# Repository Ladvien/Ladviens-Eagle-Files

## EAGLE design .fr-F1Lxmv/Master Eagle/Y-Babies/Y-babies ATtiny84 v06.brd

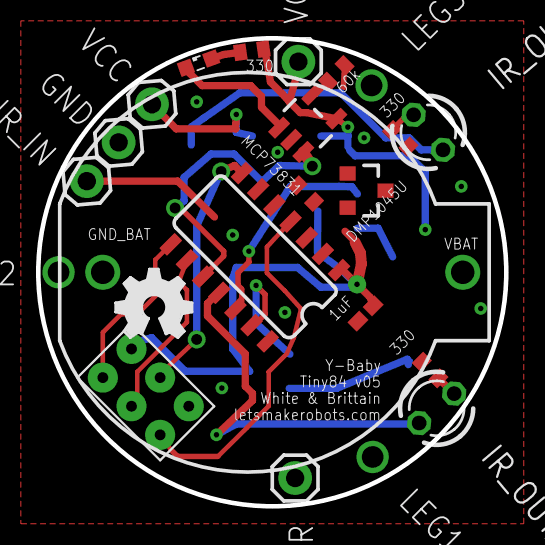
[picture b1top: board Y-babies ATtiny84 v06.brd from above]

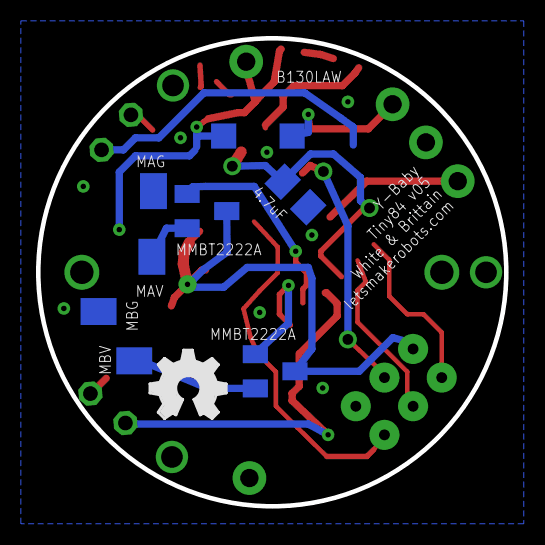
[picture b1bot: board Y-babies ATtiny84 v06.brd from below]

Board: 2 copper layers, 26.0 x 26.0 mm, 29 parts (9 on the bottom side), 20 nets.

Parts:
BAT1: LIR2032; BATTCOM_20MM_PTH
C1: 1uF; C0402K
C2: 4.7uF; C0805K
D1: B130LAW; SOD123
DMP1045U: MOSFET-PCHANNELSMD; SOT23-3
GND: M01PTH; 1X01
GND_BAR: M01PTH; 1X01
IR_IN: M01PTH; 1X01
IR_OUT_A: LED3MM
IR_OUT_B: LED3MM
LED1: SML0603
MMBT2222A_L, MMBT2222A_R: SOT23
MOT_1_A, MOT_1_B, MOT_2_A, MOT_2_B: M01SMD-4.5X1.5; PAD-1.5X4.5
R1, R2, R3: 330; R0402
R4: 60k; R0402
R5: 100k; R0402
U1: MCP73831; SOT23-5
U$1: ATTINY84; SO14
U$2: POGO_PIN_SPI_PAD
U$3, U$4: OSHW_FILLX150_NOTEXT
VCC: M01PTH; 1X01
VCC_BAR: M01PTH; 1X01

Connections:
5V: D1.A, DMP1045U.1, R3.2, R5.1, U1.4, VCC_BAR.1
GND: BAT1.2, C1.2, C2.2, GND.1, GND_BAR.1, MOT_1_A.P$1, MOT_2_B.P$1, R1.2, R2.2, R4.2, R5.2, U1.2, U$1.14, U$2.GND
IR_IN: IR_IN.1, U$1.13
IR_OUT_A: IR_OUT_A.A, U$1.11
IR_OUT_B: IR_OUT_B.A, U$1.12
MISO: U$1.8, U$2.MISO
MOSI: U$1.7, U$2.MOSI
MOT_B_IN: MMBT2222A_L.2, MOT_1_B.P$1
MOT_B_SIG: MMBT2222A_L.1, U$1.5
M_A_IN: MMBT2222A_R.2, MOT_2_A.P$1
M_A_SIG: MMBT2222A_R.1, U$1.6
unnamed: LED1.C, U1.1
unnamed: LED1.A, R3.1
unnamed: IR_OUT_A.K, R1.1
unnamed: IR_OUT_B.K, R2.1
unnamed: R4.1, U1.5
RES: U$1.4, U$2.RST
SCK: U$1.9, U$2.SCK
VBAT: BAT1.1, C2.1, DMP1045U.3, U1.3, U$1.10
VCC: C1.1, D1.C, DMP1045U.2, MMBT2222A_L.3, MMBT2222A_R.3, U$1.1, U$2.VCC, VCC.1

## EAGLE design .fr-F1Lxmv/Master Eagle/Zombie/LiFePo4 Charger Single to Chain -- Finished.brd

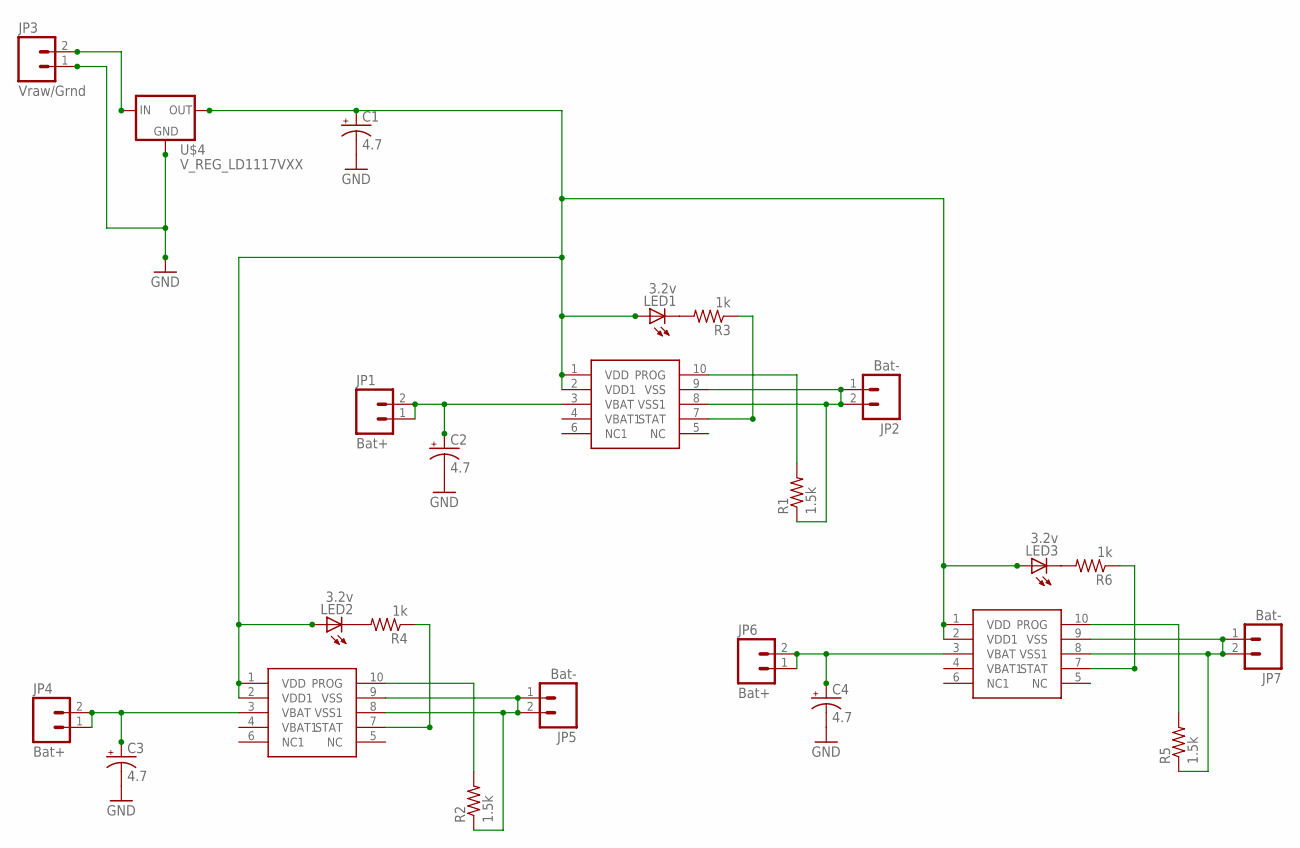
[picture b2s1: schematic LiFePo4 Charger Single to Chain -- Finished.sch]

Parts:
C1, C2, C3, C4: 4.7; CPOL-RADIAL-10UF-25V
JP1, JP4, JP6: Bat+; 1X02
JP2, JP5, JP7: Bat-; 1X02
JP3: Vraw/Grnd; 1X02
LED1, LED2, LED3: 3.2v; LED3MM
R1, R2, R5: 1.5k; 0204/7
R3, R4, R6: 1k; 0204/7
U$1, U$2, U$8: MCP73123/223
U$4: V_REG_LD1117VXX; 78XXL

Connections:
GND: C1.2 (-), C2.2 (-), C3.2 (-), C4.2 (-), JP3.1, U$4.IN (GND)
unnamed: JP3.2, U$4.OUT (IN)
unnamed: C2.1 (+), JP1.1, JP1.2, U$8.3 (VBAT)
unnamed: R1.2, U$8.10 (PROG)
unnamed: JP2.1, JP2.2, R1.1, U$8.8 (VSS1), U$8.9 (VSS)
unnamed: LED1.K (C), R3.2
unnamed: R3.1, U$8.7 (STAT)
unnamed: C3.1 (+), JP4.1, JP4.2, U$1.3 (VBAT)
unnamed: JP5.1, JP5.2, R2.1, U$1.8 (VSS1), U$1.9 (VSS)
unnamed: R4.1, U$1.7 (STAT)
unnamed: R2.2, U$1.10 (PROG)
unnamed: C4.1 (+), JP6.1, JP6.2, U$2.3 (VBAT)
unnamed: LED2.K (C), R4.2
unnamed: JP7.1, JP7.2, R5.1, U$2.8 (VSS1), U$2.9 (VSS)
unnamed: R6.1, U$2.7 (STAT)
unnamed: R5.2, U$2.10 (PROG)
unnamed: LED3.K (C), R6.2
unnamed: C1.1 (+), LED1.A, LED2.A, LED3.A, U$1.1 (VDD), U$1.2 (VDD1), U$2.1 (VDD), U$2.2 (VDD1), U$4.GND (OUT), U$8.1 (VDD), U$8.2 (VDD1)

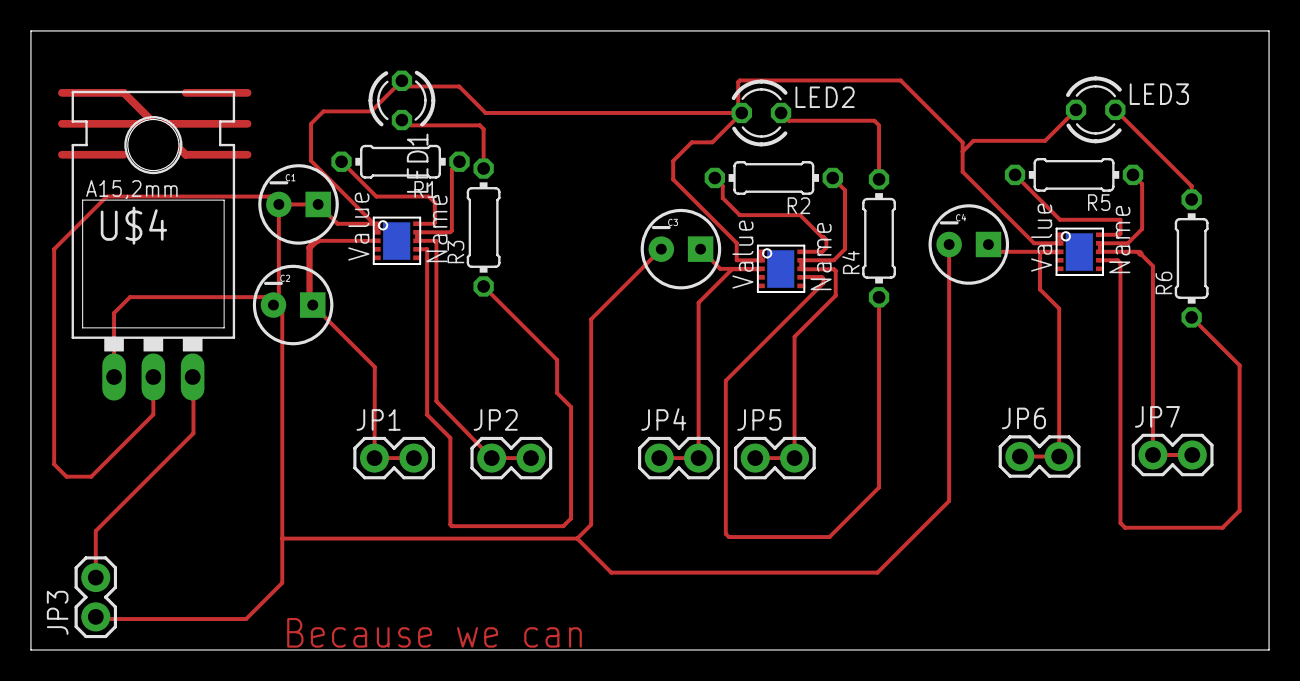
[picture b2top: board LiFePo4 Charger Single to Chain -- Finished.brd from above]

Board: 2 copper layers, 80.0 x 40.0 mm, 24 parts (0 on the bottom side), 18 nets.

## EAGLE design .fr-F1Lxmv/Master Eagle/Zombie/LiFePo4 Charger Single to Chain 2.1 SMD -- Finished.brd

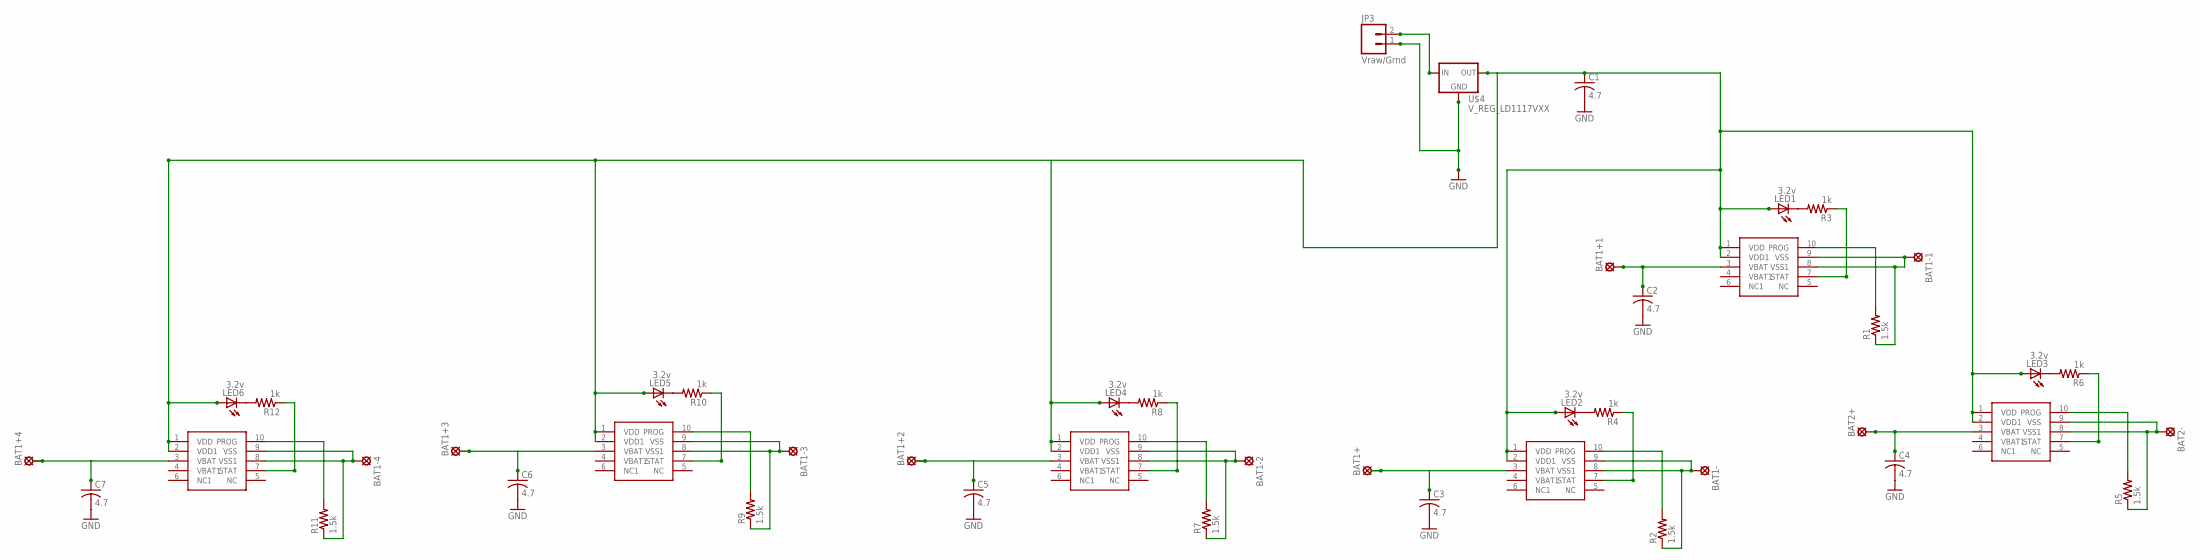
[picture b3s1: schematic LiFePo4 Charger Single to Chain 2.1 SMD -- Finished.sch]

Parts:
BAT1+, BAT1+1, BAT1+2, BAT1+3, BAT1+4, BAT1-, BAT1-1, BAT1-2, BAT1-3, BAT1-4, BAT2+, BAT2-: SE14
C1, C2, C3, C4, C5, C6, C7: 4.7; C0805
JP3: Vraw/Grnd; 1X02
LED1, LED2, LED3, LED4, LED5, LED6: 3.2v; SML0603
R1, R2, R5, R7, R9, R11: 1.5k; R0805
R3, R4, R6, R8, R10, R12: 1k; R0805
U$1, U$2, U$3, U$5, U$6, U$8: MCP73123/223
U$4: V_REG_LD1117VXX; 78XXL

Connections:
GND: C1.2, C2.2, C3.2, C4.2, C5.2, C6.2, C7.2, JP3.1, U$4.IN (GND)
unnamed: JP3.2, U$4.OUT (IN)
unnamed: BAT1+2.MP, C5.1, U$3.3 (VBAT)
unnamed: BAT1+1.MP, C2.1, U$8.3 (VBAT)
unnamed: R1.2, U$8.10 (PROG)
unnamed: BAT1-1.MP, R1.1, U$8.8 (VSS1), U$8.9 (VSS)
unnamed: LED1.C, R3.2
unnamed: R3.1, U$8.7 (STAT)
unnamed: BAT1+.MP, C3.1, U$1.3 (VBAT)
unnamed: BAT1-.MP, R2.1, U$1.8 (VSS1), U$1.9 (VSS)
unnamed: R4.1, U$1.7 (STAT)
unnamed: R2.2, U$1.10 (PROG)
unnamed: BAT2+.MP, C4.1, U$2.3 (VBAT)
unnamed: LED2.C, R4.2
unnamed: BAT2-.MP, R5.1, U$2.8 (VSS1), U$2.9 (VSS)
unnamed: R6.1, U$2.7 (STAT)
unnamed: R5.2, U$2.10 (PROG)
unnamed: LED3.C, R6.2
unnamed: C1.1, LED1.A, LED2.A, LED3.A, LED5.A, LED6.A, U$1.1 (VDD), U$1.2 (VDD1), U$2.1 (VDD), U$2.2 (VDD1), U$4.GND (OUT), U$5.1 (VDD), U$5.2 (VDD1), U$6.1 (VDD), U$6.2 (VDD1), U$8.1 (VDD), U$8.2 (VDD1)
unnamed: BAT1-2.MP, R7.1, U$3.8 (VSS1), U$3.9 (VSS)
unnamed: R8.1, U$3.7 (STAT)
unnamed: R7.2, U$3.10 (PROG)
unnamed: LED4.C, R8.2
unnamed: LED4.A, U$3.1 (VDD), U$3.2 (VDD1)
unnamed: BAT1+3.MP, C6.1, U$5.3 (VBAT)
unnamed: BAT1-3.MP, R9.1, U$5.8 (VSS1), U$5.9 (VSS)
unnamed: R10.1, U$5.7 (STAT)
unnamed: R9.2, U$5.10 (PROG)
unnamed: LED5.C, R10.2
unnamed: BAT1+4.MP, C7.1, U$6.3 (VBAT)
unnamed: BAT1-4.MP, R11.1, U$6.8 (VSS1), U$6.9 (VSS)
unnamed: R12.1, U$6.7 (STAT)
unnamed: R11.2, U$6.10 (PROG)
unnamed: LED6.C, R12.2

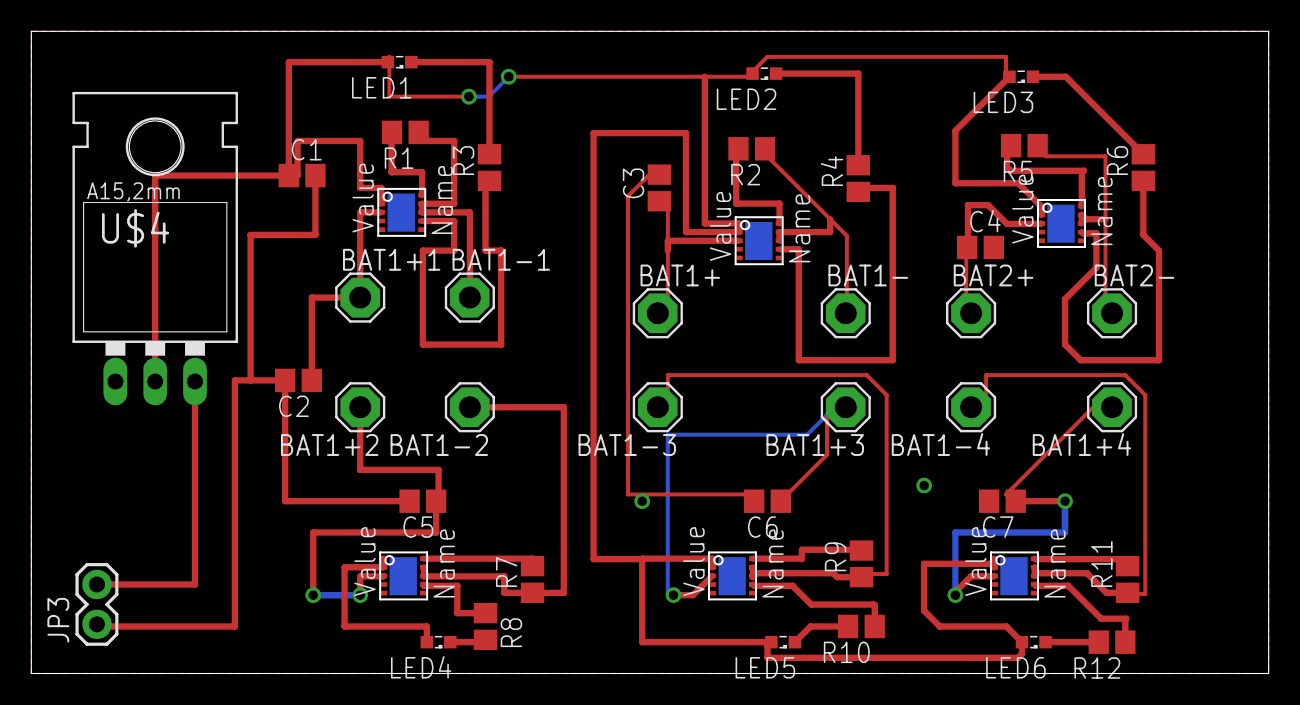
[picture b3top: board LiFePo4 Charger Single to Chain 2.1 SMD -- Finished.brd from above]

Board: 2 copper layers, 79.0 x 41.0 mm, 45 parts (0 on the bottom side), 34 nets.

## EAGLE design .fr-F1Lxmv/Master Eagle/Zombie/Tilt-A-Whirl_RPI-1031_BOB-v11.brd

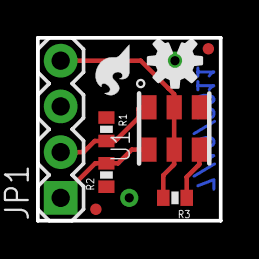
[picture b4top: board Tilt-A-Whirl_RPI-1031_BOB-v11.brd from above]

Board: 2 copper layers, 10.2 x 10.2 mm, 10 parts (0 on the bottom side), 5 nets.

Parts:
JP1: 1X04
JP2, JP3: FIDUCIAL1X2.5; FIDUCIAL-1X2.5
JP4: LOGO-SFESK; SFE-LOGO-FLAME
R1, R2: 2.2k; 0402-RES
R3: 68; 0402-RES
U1: RPI-1031
U3: CREATIVE_COMMONS
U$1: OSHW-LOGOS; OSHW-LOGO-S

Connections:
5V: JP1.4, R3.2, U1.2, U1.5
AN: R3.1, U1.6
GND: JP1.3, R1.1, R2.1, U1.3
S1: JP1.2, R1.2, U1.1
S2: JP1.1, R2.2, U1.4

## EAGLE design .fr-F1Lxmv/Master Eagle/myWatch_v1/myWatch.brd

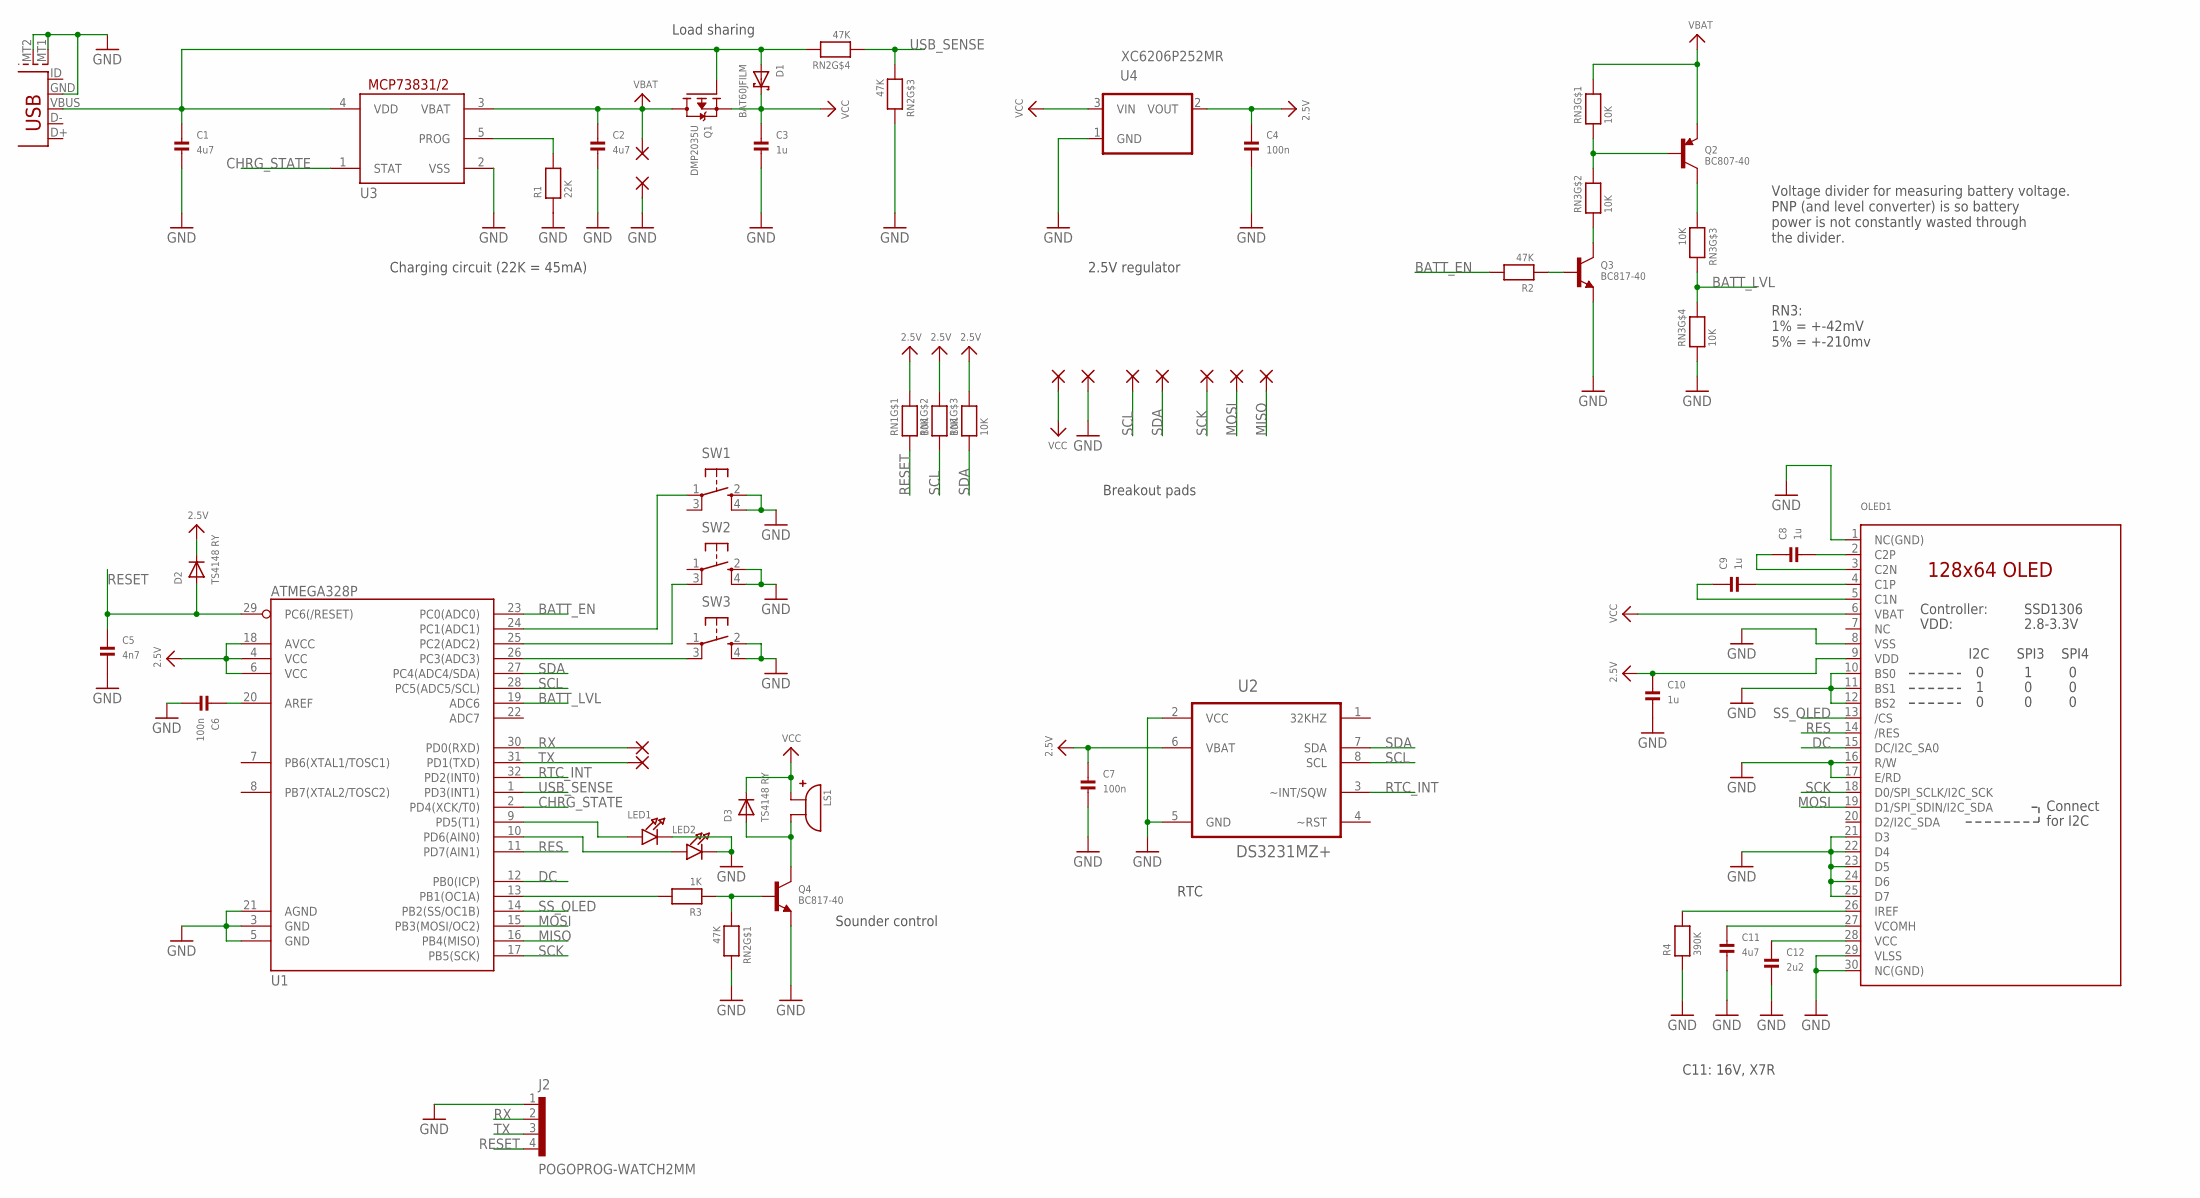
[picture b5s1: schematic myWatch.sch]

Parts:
C1, C2, C11: 4u7; 0805
C3, C8, C9, C10: 1u; 0805
C4, C6: 100n; _0402
C5: 4n7; _0402
C7: 100n; 0805
C12: 2u2; 0805
D1: BAT60JFILM; SOD-323
D2, D3: TS4148 RY; 0805_DIODE
J2: POGOPROG-WATCH2MM; POGOPROG_WATCH_2MM
LED1, LED2: LED0805; CHIPLED_0805
LS1: ABMT-801-RC; PIEZO
OLED1: DISP_OLED_UG-2864HSWEG01_NOOUTLINEWATCH; UG-2864HSWEG01_1.3_WRAPAROUND_WATCH
PAD1, PAD2, PAD3, PAD4, PAD5, PAD6, PAD7, PAD8, PAD10, PAD11, PAD12: SMD2; SMD1,27-2,54
Q1: DMP2035U; SOT23-WIDE
Q2: BC807-40; SOT23-WIDE
Q3, Q4: BC817-40; SOT23-WIDE
R1: 22K; _0402
R2: 47K; _0402
R3: 1K; _0402
R4: 390K; 0805
RN1, RN3: 10K; RESPACK_4X0603
RN2: 47K; RESPACK_4X0603
SW1, SW2, SW3: SPST_TACTRA; TACT_SMD2
U1: ATMEGA328P; TQFP32-08
U2: DS3231MZ+; SOIC8_150MIL_SMPAD
U3: MCP73832T-2ACI/OT; SOT23-5L
U4: XC6206P252MR; SOT-23
USB1: USB-MICROBLARGEPAD; USB-MICROB_LARGEPAD

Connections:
2.5V: C4.1, C7.1, C10.1, D2.2 (C), OLED1.9 (VDD), RN1.6 (2), RN1.7 (2), RN1.8 (2), U1.4 (VCC), U1.6 (VCC), U1.18 (AVCC), U2.6 (VBAT), U4.2 (VOUT)
BATT_EN: R2.2, U1.23 (PC0(ADC0))
BATT_LVL: RN3.5 (2), RN3.6 (2), U1.19 (ADC6)
CHRG_STATE: U1.2 (PD4(XCK/T0)), U3.1 (STAT)
DC: OLED1.15 (DC/I2C_SA0), U1.12 (PB0(ICP))
GND: C1.2, C2.2, C3.2, C4.2, C5.2, C6.2, C7.2, C10.2, C11.2, C12.2, J2.1, LED1.C, LED2.C, OLED1.1 (NC(GND)), OLED1.8 (VSS), OLED1.10 (BS0), OLED1.11 (BS1), OLED1.12 (BS2), OLED1.16 (R/W), OLED1.17 (E/RD), OLED1.21 (D3), OLED1.22 (D4), OLED1.23 (D5), OLED1.24 (D6), OLED1.25 (D7), OLED1.29 (VLSS), OLED1.30 (NC(GND)), PAD2.1, PAD5.1, Q3.2 (E), Q4.2 (E), R1.1, R4.1, RN2.6 (2), RN2.8 (2), RN3.4 (1), SW1.2 (S), SW1.4 (S1), SW2.2 (S), SW2.4 (S1), SW3.2 (S), SW3.4 (S1), U1.3 (GND), U1.5 (GND), U1.21 (AGND), U2.2 (VCC), U2.5 (GND), U3.2 (VSS), U4.1 (GND), USB1.GND, USB1.MT1 (SHEILD1), USB1.MT2 (SHEILD2)
MISO: PAD12.1, U1.16 (PB4(MISO))
MOSI: OLED1.19 (D1/SPI_SDIN/I2C_SDA), PAD11.1, U1.15 (PB3(MOSI/OC2))
unnamed: C6.1, U1.20 (AREF)
unnamed: SW1.1, U1.24 (PC1(ADC1))
unnamed: C8.2, OLED1.2 (C2P)
unnamed: SW3.3 (P1), U1.26 (PC3(ADC3))
unnamed: OLED1.26 (IREF), R4.2
unnamed: C1.1, D1.A, Q1.1 (G), RN2.5 (2), U3.4 (VDD), USB1.VBUS
unnamed: D3.1 (A), LS1.2 (GND), Q4.3 (C)
unnamed: Q4.1 (B), R3.1, RN2.1
unnamed: SW2.3 (P1), U1.25 (PC2(ADC2))
unnamed: R1.2, U3.5 (PROG)
unnamed: LED1.A, U1.9 (PD5(T1))
unnamed: Q2.1 (B), RN3.1, RN3.7 (2)
unnamed: C9.1, OLED1.5 (C1N)
unnamed: C9.2, OLED1.4 (C1P)
unnamed: C8.1, OLED1.3 (C2N)
unnamed: LED2.A, U1.10 (PD6(AIN0))
unnamed: Q3.3 (C), RN3.2 (1)
unnamed: Q2.3 (C), RN3.3 (1)
unnamed: C11.1, OLED1.27 (VCOMH)
unnamed: C12.1, OLED1.28 (VCC)
unnamed: Q3.1 (B), R2.1
PIEZO: R3.2, U1.13 (PB1(OC1A))
RES: OLED1.14 (/RES), U1.11 (PD7(AIN1))
RESET: C5.1, D2.1 (A), J2.4, RN1.1, U1.29 (PC6(/RESET))
RTC_INT: U1.32 (PD2(INT0)), U2.3 (~INT/SQW)
RX: J2.2, PAD3.1, U1.30 (PD0(RXD))
SCK: OLED1.18 (D0/SPI_SCLK/I2C_SCK), PAD10.1, U1.17 (PB5(SCK))
SCL: PAD8.1, RN1.2 (1), U1.28 (PC5(ADC5/SCL)), U2.8 (SCL)
SDA: PAD7.1, RN1.3 (1), U1.27 (PC4(ADC4/SDA)), U2.7 (SDA)
SS_OLED: OLED1.13 (/CS), U1.14 (PB2(SS/OC1B))
TX: J2.3, PAD4.1, U1.31 (PD1(TXD))
USB_SENSE: RN2.3 (1), RN2.4 (1), U1.1 (PD3(INT1))
VBAT: C2.1, PAD1.1, Q1.3 (D), Q2.2 (E), RN3.8 (2), U3.3 (VBAT)
VCC: C3.1, D1.C, D3.2 (C), LS1.1 (VCC), OLED1.6 (VBAT), PAD6.1, Q1.2 (S), U4.3 (VIN)

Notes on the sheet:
Charging circuit (22K = 45mA)
2.5V regulator
Voltage divider for measuring battery voltage. PNP (and level converter) is so battery power is not constantly wasted through the divider.
RTC
Load sharing
Sounder control
C11: 16V, X7R
RN3: 1% = +-42mV 5% = +-210mv
Breakout pads

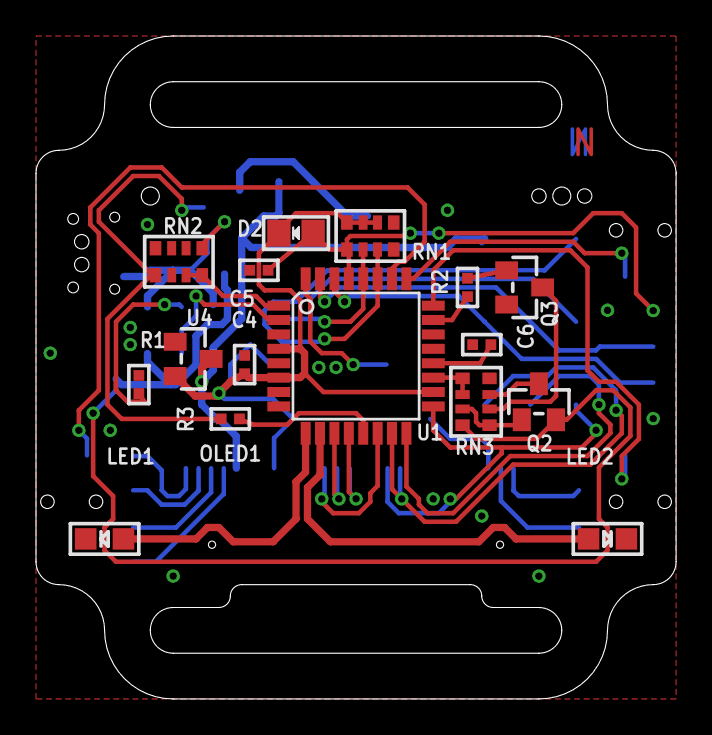
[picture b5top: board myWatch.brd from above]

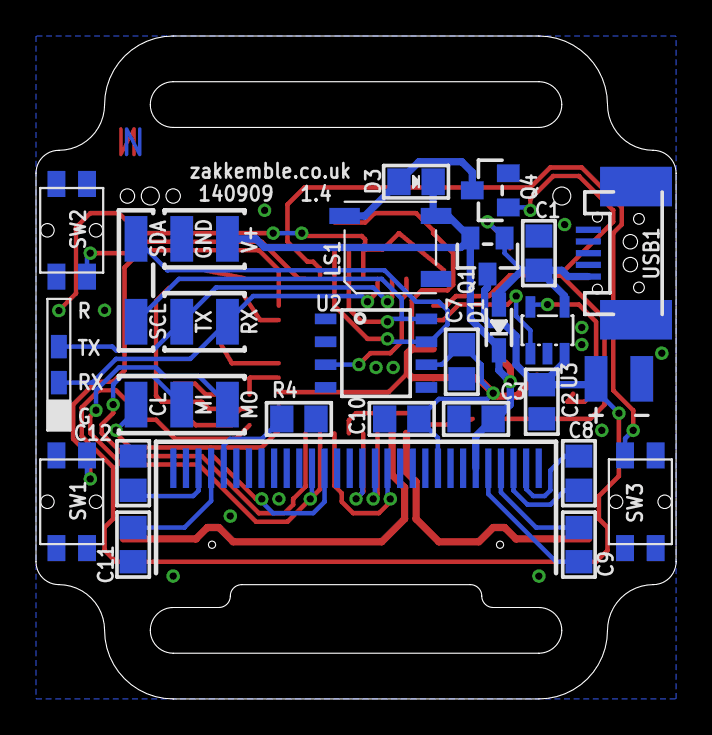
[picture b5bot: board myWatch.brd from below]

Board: 2 copper layers, 35.6 x 36.8 mm, 50 parts (33 on the bottom side), 42 nets.

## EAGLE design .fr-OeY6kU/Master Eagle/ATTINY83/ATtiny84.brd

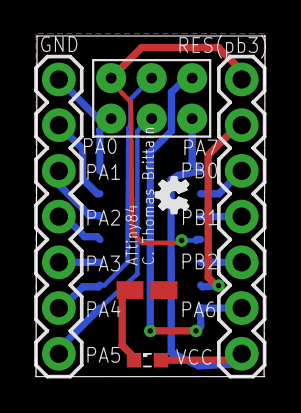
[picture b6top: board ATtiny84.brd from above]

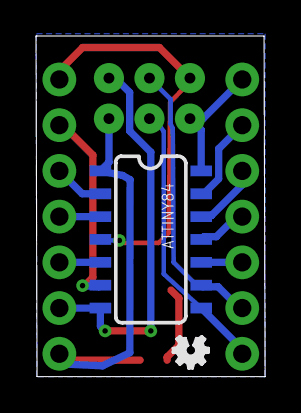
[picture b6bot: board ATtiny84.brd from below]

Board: 2 copper layers, 12.7 x 18.9 mm, 8 parts (2 on the bottom side), 15 nets.

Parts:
ATTINY84: ATTINY84; SO14
JP1, JP2: 1X07
LED1: SML0603
R1: R0805W
U$1, U$3: OSHW_FILLX70_NOTEXT
U$2: POGO_PIN_SPI_PAD

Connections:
GND: ATTINY84.14, JP2.7, R1.1, U$2.GND
unnamed: LED1.C, R1.2
PA0: ATTINY84.13, JP2.6
PA1: ATTINY84.12, JP2.5
PA2: ATTINY84.11, JP2.4
PA3: ATTINY84.10, JP2.3
PA4: ATTINY84.9, JP2.2, U$2.SCK
PA5: ATTINY84.8, JP2.1, U$2.MOSI
PA6: ATTINY84.7, JP1.2, U$2.MISO
PA7: ATTINY84.6, JP1.6
PB0: ATTINY84.2, JP1.5
PB1: ATTINY84.3, JP1.4
PB2: ATTINY84.5, JP1.3
PB3: ATTINY84.4, JP1.7, U$2.RST
VCC: ATTINY84.1, JP1.1, LED1.A, U$2.VCC

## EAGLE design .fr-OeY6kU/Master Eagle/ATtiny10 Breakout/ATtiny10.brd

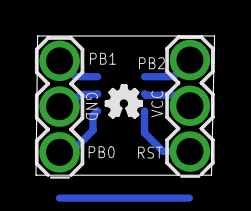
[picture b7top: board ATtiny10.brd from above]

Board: 2 copper layers, 9.9 x 7.7 mm, 4 parts (1 on the bottom side), 6 nets.

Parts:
IC1: ATTINY10; SOT23-6
U$1, U$2: 1X3_SHORT_ROUND
U$3: OSHW_FILLX70_NOTEXT

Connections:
GND: IC1.2, U$1.2
PB0: IC1.1, U$1.3
PB1: IC1.3, U$1.1
PB2: IC1.4, U$2.1
RST: IC1.6, U$2.3
VCC: IC1.5, U$2.2

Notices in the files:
parts and their libraries:
SparkFun: Licensing: CC v3.0 Share-Alike You are welcome to use this library for commercial purposes.
SparkFun: Released under the Creative Commons Attribution Share-Alike 3.0 License
SparkFun: http://creativecommons.org/licenses/by-sa/3.0
